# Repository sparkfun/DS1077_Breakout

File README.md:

DS1077 Breakout
===============

[
*DS1077 Programmable Oscillator (BOB-09116)*](https://www.sparkfun.com/products/9116)

This is a breakout for the DS1077 Programmable Oscillator - 16.2kHz to 133MHz.
The board communicates via a 2-wire serial interface. 

Repository Contents
-------------------
* **/Firmware** - Example firmware to operate the board
* **/Hardware** - All Eagle design files (.brd, .sch)
* **/Production** - Test bed files and production panel files

License Information
-------------------
The hardware is released under [Creative Commons ShareAlike 4.0 International](https://creativecommons.org/licenses/by-sa/4.0/).
The code is beerware; if you see me (or any other SparkFun employee) at the local, and you've found our code helpful, please buy us a round!

Distributed as-is; no warranty is given.

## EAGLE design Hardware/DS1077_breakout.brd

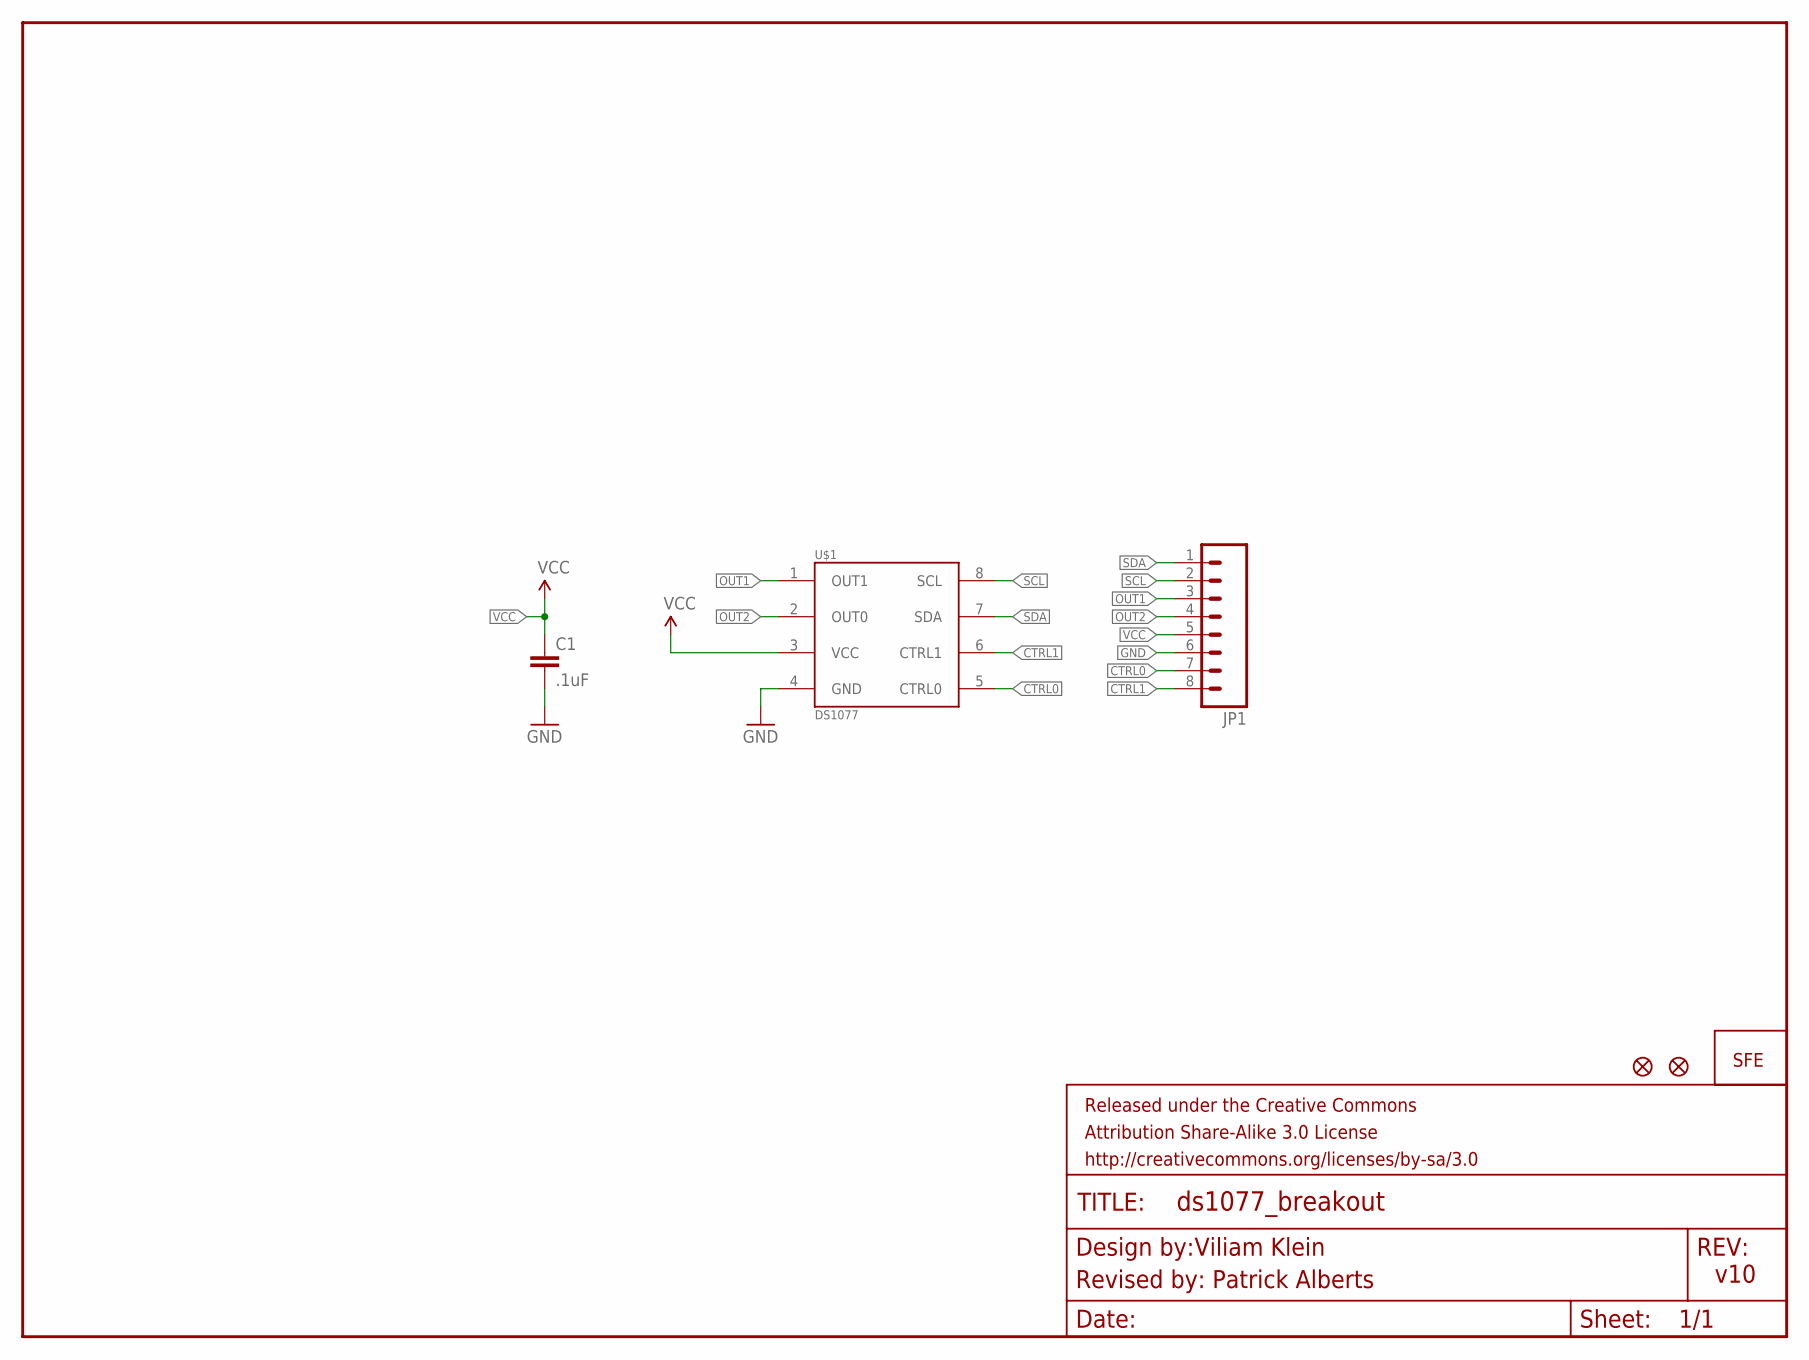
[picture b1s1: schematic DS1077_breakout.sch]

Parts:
C1: .1uF; 0603
FRAME1: FRAME-LETTER; CREATIVE_COMMONS
JP1: M081X08; 1X08
U$1: DS1077; SO08
U$2: LOGO-SFESK; SFE-LOGO-FLAME
U$3, U$4: FIDUCIAL1X2; FIDUCIAL-1X2

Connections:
CTRL0: JP1.7, U$1.5 (CTRL0)
CTRL1: JP1.8, U$1.6 (CTRL1)
GND: C1.2, JP1.6, U$1.4 (GND)
OUT1: JP1.3, U$1.1 (OUT1)
OUT2: JP1.4, U$1.2 (OUT0)
SCL: JP1.2, U$1.8 (SCL)
SDA: JP1.1, U$1.7 (SDA)
VCC: C1.1, JP1.5, U$1.3 (VCC)

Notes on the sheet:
v10
Viliam Klein
Revised by: Patrick Alberts

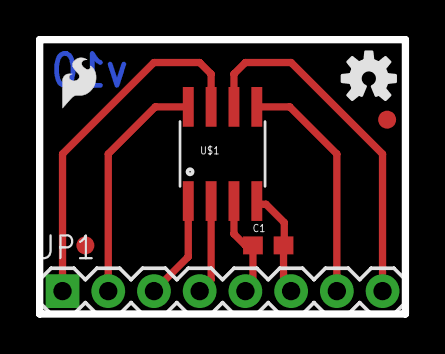
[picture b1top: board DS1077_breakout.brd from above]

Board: 2 copper layers, 20.3 x 15.2 mm, 8 parts (0 on the bottom side), 8 nets.

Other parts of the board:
U$5: OSHW-LOGO-S

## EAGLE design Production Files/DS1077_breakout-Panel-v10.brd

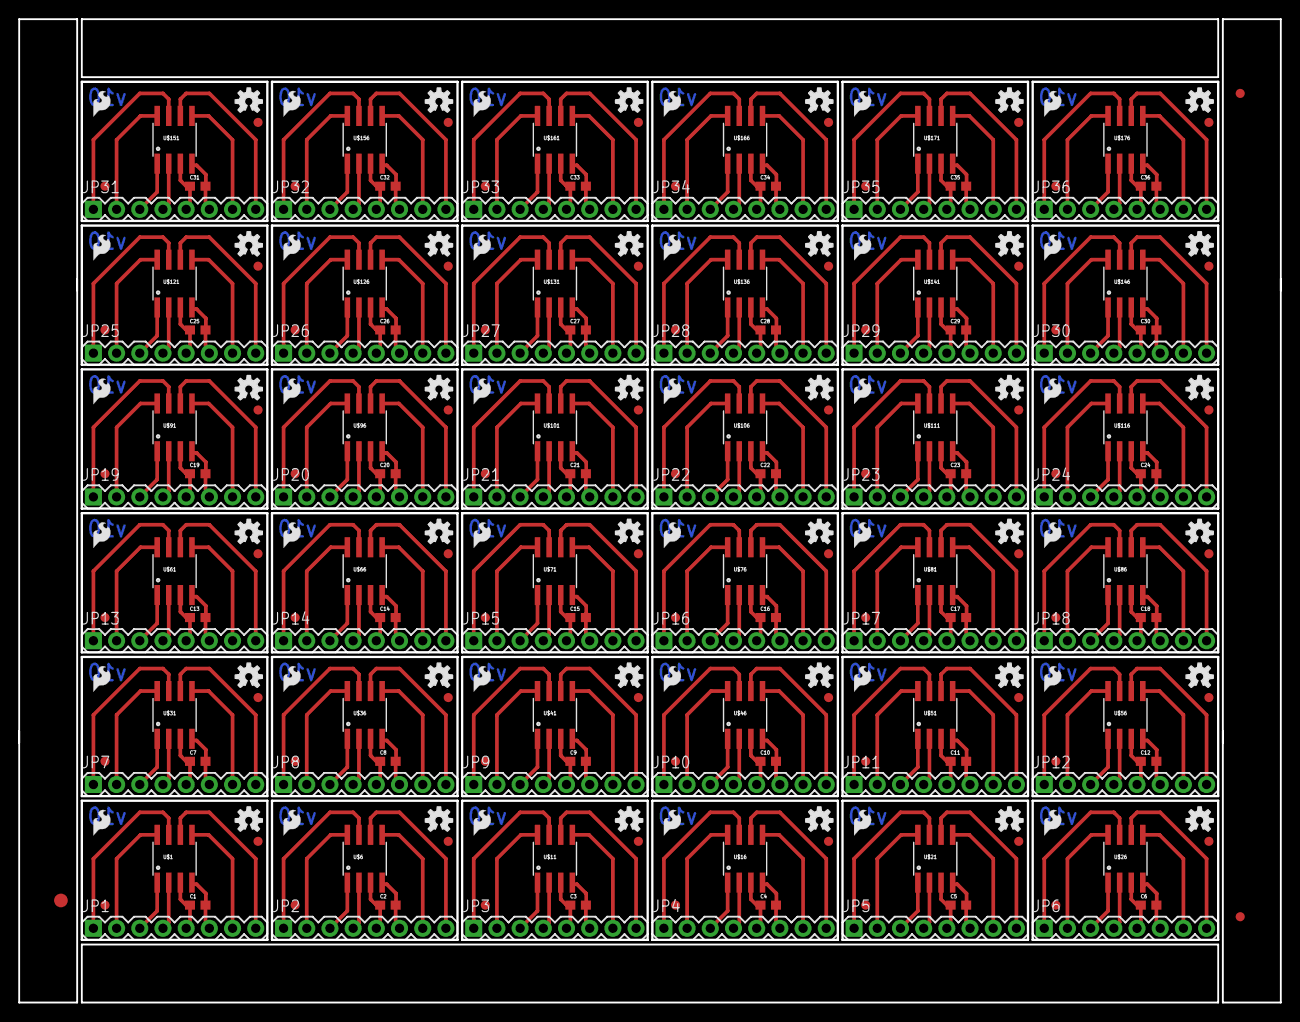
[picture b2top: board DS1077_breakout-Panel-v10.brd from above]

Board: 2 copper layers, 138.1 x 107.6 mm, 255 parts (0 on the bottom side), 288 nets.

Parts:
C1, C2, C3, C4, C5, C6, C7, C8, C9, C10, C11, C12, C13, C14, C15, C16, C17, C18, C19, C20, C21, C22, C23, C24, C25, C26, C27, C28, C29, C30, C31, C32, C33, C34, C35, C36: .1uF; 0603
E$1: FIDUCIAL-1.5X3
E$4, E$5: FIDUCIAL-1X2
JP1, JP2, JP3, JP4, JP5, JP6, JP7, JP8, JP9, JP10, JP11, JP12, JP13, JP14, JP15, JP16, JP17, JP18, JP19, JP20, JP21, JP22, JP23, JP24, JP25, JP26, JP27, JP28, JP29, JP30, JP31, JP32, JP33, JP34, JP35, JP36: 1X08
U$1, U$6, U$11, U$16, U$21, U$26, U$31, U$36, U$41, U$46, U$51, U$56, U$61, U$66, U$71, U$76, U$81, U$86, U$91, U$96, U$101, U$106, U$111, U$116, U$121, U$126, U$131, U$136, U$141, U$146, U$151, U$156, U$161, U$166, U$171, U$176: DS1077; SO08
U$2, U$7, U$12, U$17, U$22, U$27, U$32, U$37, U$42, U$47, U$52, U$57, U$62, U$67, U$72, U$77, U$82, U$87, U$92, U$97, U$102, U$107, U$112, U$117, U$122, U$127, U$132, U$137, U$142, U$147, U$152, U$157, U$162, U$167, U$172, U$177: LOGO-SFESK; SFE-LOGO-FLAME
U$3, U$4, U$8, U$9, U$13, U$14, U$18, U$19, U$23, U$24, U$28, U$29, U$33, U$34, U$38, U$39, U$43, U$44, U$48, U$49, U$53, U$54, U$58, U$59, U$63, U$64, U$68, U$69, U$73, U$74, U$78, U$79, U$83, U$84, U$88, U$89, U$93, U$94, U$98, U$99, U$103, U$104, U$108, U$109, U$113, U$114, U$118, U$119, U$123, U$124, U$128, U$129, U$133, U$134, U$138, U$139, U$143, U$144, U$148, U$149, U$153, U$154, U$158, U$159, U$163, U$164, U$168, U$169, U$173, U$174, U$178, U$179: FIDUCIAL1X2; FIDUCIAL-1X2
U$5, U$10, U$15, U$20, U$25, U$30, U$35, U$40, U$45, U$50, U$55, U$60, U$65, U$70, U$75, U$80, U$85, U$90, U$95, U$100, U$105, U$110, U$115, U$120, U$125, U$130, U$135, U$140, U$145, U$150, U$155, U$160, U$165, U$170, U$175, U$180: OSHW-LOGO-S

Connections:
CTRL0: JP1.7, U$1.5
CTRL1: JP1.8, U$1.6
CTRL2: JP2.7, U$6.5
CTRL3: JP2.8, U$6.6
CTRL4: JP3.7, U$11.5
CTRL5: JP3.8, U$11.6
CTRL6: JP4.7, U$16.5
CTRL7: JP4.8, U$16.6
CTRL8: JP5.7, U$21.5
CTRL9: JP5.8, U$21.6
CTRL10: JP6.7, U$26.5
CTRL11: JP6.8, U$26.6
CTRL12: JP7.7, U$31.5
CTRL13: JP7.8, U$31.6
CTRL14: JP8.7, U$36.5
CTRL15: JP8.8, U$36.6
CTRL16: JP9.7, U$41.5
CTRL17: JP9.8, U$41.6
CTRL18: JP10.7, U$46.5
CTRL19: JP10.8, U$46.6
CTRL20: JP11.7, U$51.5
CTRL21: JP11.8, U$51.6
CTRL22: JP12.7, U$56.5
CTRL23: JP12.8, U$56.6
CTRL24: JP13.7, U$61.5
CTRL25: JP13.8, U$61.6
CTRL26: JP14.7, U$66.5
CTRL27: JP14.8, U$66.6
CTRL28: JP15.7, U$71.5
CTRL29: JP15.8, U$71.6
CTRL30: JP16.7, U$76.5
CTRL31: JP16.8, U$76.6
CTRL32: JP17.7, U$81.5
CTRL33: JP17.8, U$81.6
CTRL34: JP18.7, U$86.5
CTRL35: JP18.8, U$86.6
CTRL36: JP19.7, U$91.5
CTRL37: JP19.8, U$91.6
CTRL38: JP20.7, U$96.5
CTRL39: JP20.8, U$96.6
CTRL40: JP21.7, U$101.5
CTRL41: JP21.8, U$101.6
CTRL42: JP22.7, U$106.5
CTRL43: JP22.8, U$106.6
CTRL44: JP23.7, U$111.5
CTRL45: JP23.8, U$111.6
CTRL46: JP24.7, U$116.5
CTRL47: JP24.8, U$116.6
CTRL48: JP25.7, U$121.5
CTRL49: JP25.8, U$121.6
CTRL50: JP26.7, U$126.5
CTRL51: JP26.8, U$126.6
CTRL52: JP27.7, U$131.5
CTRL53: JP27.8, U$131.6
CTRL54: JP28.7, U$136.5
CTRL55: JP28.8, U$136.6
CTRL56: JP29.7, U$141.5
CTRL57: JP29.8, U$141.6
CTRL58: JP30.7, U$146.5
CTRL59: JP30.8, U$146.6
CTRL60: JP31.7, U$151.5
CTRL61: JP31.8, U$151.6
CTRL62: JP32.7, U$156.5
CTRL63: JP32.8, U$156.6
CTRL64: JP33.7, U$161.5
CTRL65: JP33.8, U$161.6
CTRL66: JP34.7, U$166.5
CTRL67: JP34.8, U$166.6
CTRL68: JP35.7, U$171.5
CTRL69: JP35.8, U$171.6
CTRL70: JP36.7, U$176.5
CTRL71: JP36.8, U$176.6
GND: C1.2, JP1.6, U$1.4
GND1: C2.2, JP2.6, U$6.4
GND2: C3.2, JP3.6, U$11.4
GND3: C4.2, JP4.6, U$16.4
GND4: C5.2, JP5.6, U$21.4
GND5: C6.2, JP6.6, U$26.4
GND6: C7.2, JP7.6, U$31.4
GND7: C8.2, JP8.6, U$36.4
GND8: C9.2, JP9.6, U$41.4
GND9: C10.2, JP10.6, U$46.4
GND10: C11.2, JP11.6, U$51.4
GND11: C12.2, JP12.6, U$56.4
GND12: C13.2, JP13.6, U$61.4
GND13: C14.2, JP14.6, U$66.4
GND14: C15.2, JP15.6, U$71.4
GND15: C16.2, JP16.6, U$76.4
GND16: C17.2, JP17.6, U$81.4
GND17: C18.2, JP18.6, U$86.4
GND18: C19.2, JP19.6, U$91.4
GND19: C20.2, JP20.6, U$96.4
GND20: C21.2, JP21.6, U$101.4
GND21: C22.2, JP22.6, U$106.4
GND22: C23.2, JP23.6, U$111.4
GND23: C24.2, JP24.6, U$116.4
GND24: C25.2, JP25.6, U$121.4
GND25: C26.2, JP26.6, U$126.4
GND26: C27.2, JP27.6, U$131.4
GND27: C28.2, JP28.6, U$136.4
GND28: C29.2, JP29.6, U$141.4
GND29: C30.2, JP30.6, U$146.4
GND30: C31.2, JP31.6, U$151.4
GND31: C32.2, JP32.6, U$156.4
GND32: C33.2, JP33.6, U$161.4
GND33: C34.2, JP34.6, U$166.4
GND34: C35.2, JP35.6, U$171.4
GND35: C36.2, JP36.6, U$176.4
OUT1: JP1.3, U$1.1
OUT2: JP1.4, U$1.2
OUT3: JP2.3, U$6.1
OUT4: JP2.4, U$6.2
OUT5: JP3.3, U$11.1
OUT6: JP3.4, U$11.2
OUT7: JP4.3, U$16.1
OUT8: JP4.4, U$16.2
OUT9: JP5.3, U$21.1
OUT10: JP5.4, U$21.2
OUT11: JP6.3, U$26.1
OUT12: JP6.4, U$26.2
OUT13: JP7.3, U$31.1
OUT14: JP7.4, U$31.2
OUT15: JP8.3, U$36.1
OUT16: JP8.4, U$36.2
OUT17: JP9.3, U$41.1
OUT18: JP9.4, U$41.2
OUT19: JP10.3, U$46.1
OUT20: JP10.4, U$46.2
OUT21: JP11.3, U$51.1
OUT22: JP11.4, U$51.2
OUT23: JP12.3, U$56.1
OUT24: JP12.4, U$56.2
OUT25: JP13.3, U$61.1
OUT26: JP13.4, U$61.2
OUT27: JP14.3, U$66.1
OUT28: JP14.4, U$66.2
OUT29: JP15.3, U$71.1
OUT30: JP15.4, U$71.2
OUT31: JP16.3, U$76.1
OUT32: JP16.4, U$76.2
OUT33: JP17.3, U$81.1
OUT34: JP17.4, U$81.2
OUT35: JP18.3, U$86.1
OUT36: JP18.4, U$86.2
OUT37: JP19.3, U$91.1
OUT38: JP19.4, U$91.2
OUT39: JP20.3, U$96.1
OUT40: JP20.4, U$96.2
OUT41: JP21.3, U$101.1
OUT42: JP21.4, U$101.2
OUT43: JP22.3, U$106.1
OUT44: JP22.4, U$106.2
OUT45: JP23.3, U$111.1
OUT46: JP23.4, U$111.2
OUT47: JP24.3, U$116.1
OUT48: JP24.4, U$116.2
OUT49: JP25.3, U$121.1
OUT50: JP25.4, U$121.2
OUT51: JP26.3, U$126.1
OUT52: JP26.4, U$126.2
OUT53: JP27.3, U$131.1
OUT54: JP27.4, U$131.2
OUT55: JP28.3, U$136.1
OUT56: JP28.4, U$136.2
OUT57: JP29.3, U$141.1
OUT58: JP29.4, U$141.2
OUT59: JP30.3, U$146.1
OUT60: JP30.4, U$146.2
OUT61: JP31.3, U$151.1
OUT62: JP31.4, U$151.2
OUT63: JP32.3, U$156.1
OUT64: JP32.4, U$156.2
OUT65: JP33.3, U$161.1
OUT66: JP33.4, U$161.2
OUT67: JP34.3, U$166.1
OUT68: JP34.4, U$166.2
OUT69: JP35.3, U$171.1
OUT70: JP35.4, U$171.2
OUT71: JP36.3, U$176.1
OUT72: JP36.4, U$176.2
SCL: JP1.2, U$1.8
SCL1: JP2.2, U$6.8
SCL2: JP3.2, U$11.8
SCL3: JP4.2, U$16.8
SCL4: JP5.2, U$21.8
SCL5: JP6.2, U$26.8
SCL6: JP7.2, U$31.8
SCL7: JP8.2, U$36.8
SCL8: JP9.2, U$41.8
SCL9: JP10.2, U$46.8
SCL10: JP11.2, U$51.8
SCL11: JP12.2, U$56.8
SCL12: JP13.2, U$61.8
SCL13: JP14.2, U$66.8
SCL14: JP15.2, U$71.8
SCL15: JP16.2, U$76.8
SCL16: JP17.2, U$81.8
SCL17: JP18.2, U$86.8
SCL18: JP19.2, U$91.8
SCL19: JP20.2, U$96.8
SCL20: JP21.2, U$101.8
SCL21: JP22.2, U$106.8
SCL22: JP23.2, U$111.8
SCL23: JP24.2, U$116.8
SCL24: JP25.2, U$121.8
SCL25: JP26.2, U$126.8
SCL26: JP27.2, U$131.8
SCL27: JP28.2, U$136.8
SCL28: JP29.2, U$141.8
SCL29: JP30.2, U$146.8
SCL30: JP31.2, U$151.8
SCL31: JP32.2, U$156.8
SCL32: JP33.2, U$161.8
SCL33: JP34.2, U$166.8
SCL34: JP35.2, U$171.8
SCL35: JP36.2, U$176.8
SDA: JP1.1, U$1.7
SDA1: JP2.1, U$6.7
SDA2: JP3.1, U$11.7
SDA3: JP4.1, U$16.7
SDA4: JP5.1, U$21.7
SDA5: JP6.1, U$26.7
SDA6: JP7.1, U$31.7
SDA7: JP8.1, U$36.7
SDA8: JP9.1, U$41.7
SDA9: JP10.1, U$46.7
SDA10: JP11.1, U$51.7
SDA11: JP12.1, U$56.7
SDA12: JP13.1, U$61.7
SDA13: JP14.1, U$66.7
SDA14: JP15.1, U$71.7
SDA15: JP16.1, U$76.7
SDA16: JP17.1, U$81.7
SDA17: JP18.1, U$86.7
SDA18: JP19.1, U$91.7
SDA19: JP20.1, U$96.7
SDA20: JP21.1, U$101.7
SDA21: JP22.1, U$106.7
SDA22: JP23.1, U$111.7
SDA23: JP24.1, U$116.7
SDA24: JP25.1, U$121.7
SDA25: JP26.1, U$126.7
SDA26: JP27.1, U$131.7
SDA27: JP28.1, U$136.7
SDA28: JP29.1, U$141.7
SDA29: JP30.1, U$146.7
SDA30: JP31.1, U$151.7
SDA31: JP32.1, U$156.7
SDA32: JP33.1, U$161.7
SDA33: JP34.1, U$166.7
SDA34: JP35.1, U$171.7
SDA35: JP36.1, U$176.7
VCC: C1.1, JP1.5, U$1.3
VCC1: C2.1, JP2.5, U$6.3
VCC2: C3.1, JP3.5, U$11.3
VCC3: C4.1, JP4.5, U$16.3
VCC4: C5.1, JP5.5, U$21.3
VCC5: C6.1, JP6.5, U$26.3
VCC6: C7.1, JP7.5, U$31.3
VCC7: C8.1, JP8.5, U$36.3
VCC8: C9.1, JP9.5, U$41.3
VCC9: C10.1, JP10.5, U$46.3
VCC10: C11.1, JP11.5, U$51.3
VCC11: C12.1, JP12.5, U$56.3
VCC12: C13.1, JP13.5, U$61.3
VCC13: C14.1, JP14.5, U$66.3
VCC14: C15.1, JP15.5, U$71.3
VCC15: C16.1, JP16.5, U$76.3
VCC16: C17.1, JP17.5, U$81.3
VCC17: C18.1, JP18.5, U$86.3
VCC18: C19.1, JP19.5, U$91.3
VCC19: C20.1, JP20.5, U$96.3
VCC20: C21.1, JP21.5, U$101.3
VCC21: C22.1, JP22.5, U$106.3
VCC22: C23.1, JP23.5, U$111.3
VCC23: C24.1, JP24.5, U$116.3
VCC24: C25.1, JP25.5, U$121.3
VCC25: C26.1, JP26.5, U$126.3
VCC26: C27.1, JP27.5, U$131.3
VCC27: C28.1, JP28.5, U$136.3
VCC28: C29.1, JP29.5, U$141.3
VCC29: C30.1, JP30.5, U$146.3
VCC30: C31.1, JP31.5, U$151.3
VCC31: C32.1, JP32.5, U$156.3
VCC32: C33.1, JP33.5, U$161.3
VCC33: C34.1, JP34.5, U$166.3
VCC34: C35.1, JP35.5, U$171.3
VCC35: C36.1, JP36.5, U$176.3

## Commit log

2014-01-22 Added Brd/Sch Files
2014-02-11 Updated vias/schematic/ver#
    Updated vias, schematic and version number as well as adding the OSH
    logo.
2014-02-11 created panel v10
    Skadoosh
2014-05-12 Adding firmware, updating README

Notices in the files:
parts and their libraries:
SparkFun-Aesthetics: Licensing: CC v3.0 Share-Alike You are welcome to use this library for commercial purposes.
SparkFun-Aesthetics: Released under the Creative Commons Attribution Share-Alike 3.0 License
SparkFun-Aesthetics: http://creativecommons.org/licenses/by-sa/3.0
